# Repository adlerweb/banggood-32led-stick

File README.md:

This repository contains hardware documentation and software for Banggoods ["DIY 32 Bit LED Shake Stick Kit"](http://goo.gl/JAC3Vc). This repository is a supplement for [BitBastelei #205](https://www.adlerweb.info/blog/2016/07/24/bitbastelei-205-diy-32-bit-led-shake-stick-kit-banggood)(German).

# Hardware

The design itself is based on a [STC11F02E microcontroller](http://www.stcmcu.com/datasheet/stc/STC-AD-PDF/STC11F-10Fxx-english.pdf) (8051-compatible, 2KB Flash, 2KB EEPROM). All LEDs are connectred in a 3-way-matrix (lines, rows and polarity). An additional direction-switch and a push button are also available. The chip can be programmed using a serial connection which is available on a separate pin header.

Design notes:
 * While the battery case is build for 4xAA you should only use 3 and short the last one to avoid overvoltage. [See Instructions](http://forum.banggood.com/forum-topic-149391.html).
 * LEDs are not current limited and must be pulsed quickly to avoid damage
 * The IC is inteded for <=20mA and most likely overused

The provided design files can be opened using [KiCad](http://kicad-pcb.org/). The schematic schould be correct, the board layout is only a coarse drawing and should not be used as a reference without further checks 

# Software

The software is written in C and intended to be compiled using [sdcc](http://sdcc.sourceforge.net/). A project file for [MCU 8051 IDE](http://www.moravia-microsystems.com/mcu-8051-ide/) is included. Both tools are available for linux under a open source license, Windows-Versions should also be available.

In it's current state some basic functionallity is given, but the software is far from complere, see below for a list of known flaws.

## How the software works

At the top of the file a array of longs is defined. Every element represents one column of 32 LEDs, the left/highest bit will be drawn at the base of the unit. The first element will be drawn first. You can make the array wider or smaller using GRAPHSIZE above.

To draw a column the code will iterate every LED, switching the corresponding ports for LEDs to be lit either LOW or HIGH accordingly. LEDs and pins not used well be set to High-Z to avoid involuntary driving of other LEDs on the lines/columns of the LED-array. 

The main program will first inizialize all ports as inputs (High-Z) with an exception for both buttons which will be driven using the "quasi bidirectional" mode, allowing us to use the MCU as pull-up.

The main loop will start drawing once the push-button is pressed. This should be replaced with the direction switch for proper drawing. It will begin using the first array element and draw it several times. If the timeout is up it will continue with the second column, etc. Drawing will automatically stop when reaching the last element or releasing the button.

The timeout is calculated dynamically, the code will start with one and increase the number of repetition if the draw was finished before releasing the button (of later changing the direction again). Thes isn't really feasible when using the push-button but should somewhat work one the direction switch is used.

## How the software should work

Have a nice whish-list of things, that should be improved…

* Fix the direction-switch. I wasn't able to get the direction switch working right away and the push-button was enough for demonstration. Shouldn't be too much work
* The graph should be stored in EEPROM instead of flash memory as it is now - this should noticably increase available space and should allow for multiple graphs
* A more or less intelligent way to compress the graphs may also free up space, but I'm not sure if loosing the human-redability and a lot of processing power is worth the effort
* The 2-line-speed-algorithm may need a bit of care to be reliable
* Currently every LED is driven separatly. While this is easy to implement and keeps the current down it is also fscking slow. Grouping lines, columns or whatever should save execution time and allow for higher horizontal resolution and nicer text
*  It should be possible to implement a basic font and add a "programming mode" (power up with button pressed?) to allow for easier customization without the need to recompile the code every time

## Flashing

The IC can be programmed using a serial bootloader. You need a USB so TTL serial adapter to connect your PC to the board. Connect GND to GND, VCC to VCC/5V and cross RX/TX. On the software side you can use [stcgal](https://github.com/grigorig/stcgal) on linux or [the official tool](http://www.stcmcu.com/STCISP/stc-isp-15xx-v6.63.exe) for windows (which is afaik not in english…). You have to start the flashing process on your PC first and then powercycle the IC to enter the serial bootloader.

For Linux you can use this command:

```stcgal -P stc12 -p /dev/ttyUSB0 main.hex```

Yes, the LED-board is using a stc11-IC, but the protocol is identical. Please be aware you need full access to your serial programmer, depending on your setup you have to start the process as root or use sudo.

# Thanks

* [Banggood](http://banggood.com) for sponsoring the kit (and getting me to learn 8051-C)
* [Grigori Goronzy and all stcgal contributors](https://github.com/grigorig/stcgal) for saving me from wine with chinese fonts
* The team behind [sdcc](http://sdcc.sourceforge.net/) so I'm not required to write my own STC11 header files
* The guys behind [MCU 8051 IDE](http://www.moravia-microsystems.com/mcu-8051-ide/) so I hadn't to read the sdcc man page
* The whole [KiCad](http://kicad-pcb.org/) Folks because it still rocks
* You for providing patches, right? ;)

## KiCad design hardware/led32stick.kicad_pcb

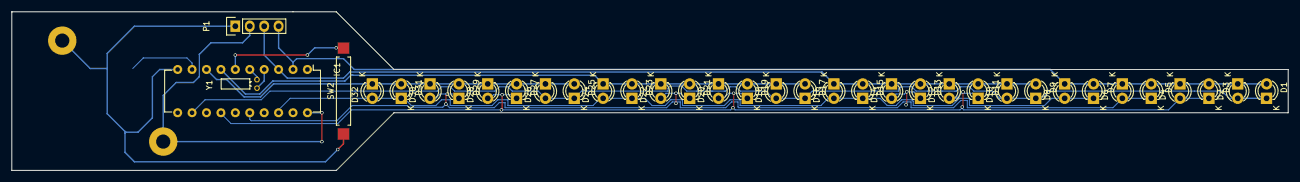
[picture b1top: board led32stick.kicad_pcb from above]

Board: 2 copper layers, 224.8 x 27.9 mm, 38 parts (1 on the bottom side), 14 nets.

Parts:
BT1: 3xAA; WireConnection_2.50mmDrill
D1, D2, D3, D4, D5, D6, D7, D8, D9, D10, D11, D12, D13, D14, D15, D16, D17, D18, D19, D20, D21, D22, D23, D24, D25, D26, D27, D28, D29, D30, D31, D32: LED; LED-3MM
IC1: STC11Fxx; DIP-20_W7.62mm
P1: CONN_01X04; Pin_Header_Straight_1x04
SW1: SW_PUSH; SW_SPST_B3S-1000
SW2: SPST; SW_SPST_REED_CT10-XXXX-G1
Y1: 12MHz; Crystal_Round_Horizontal_2mm

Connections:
GND: BT1.2, IC1.10, P1.1, SW1.2, SW2.2
unnamed: D1.1, D2.2, D9.1, D10.2, D17.1, D18.2, D25.1, D26.2, IC1.12
unnamed: D1.2, D2.1, D3.2, D4.1, D5.2, D6.1, D7.2, D8.1, IC1.2, P1.4
unnamed: D9.2, D10.1, D11.2, D12.1, D13.2, D14.1, D15.2, D16.1, IC1.3, P1.3
unnamed: D3.1, D4.2, D11.1, D12.2, D19.1, D20.2, D27.1, D28.2, IC1.14
unnamed: D5.1, D6.2, D13.1, D14.2, D21.1, D22.2, D29.1, D30.2, IC1.16
unnamed: D7.1, D8.2, D15.1, D16.2, D23.1, D24.2, D31.1, D32.2, IC1.18
unnamed: D17.2, D18.1, D19.2, D20.1, D21.2, D22.1, D23.2, D24.1, IC1.7
unnamed: D25.2, D26.1, D27.2, D28.1, D29.2, D30.1, D31.2, D32.1, IC1.8
unnamed: IC1.4, Y1.1
unnamed: IC1.5, Y1.2
unnamed: IC1.6, SW2.1
unnamed: IC1.9, SW1.1
VCC: BT1.1, IC1.20, P1.2

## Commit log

2016-07-23 Import Software
2016-07-23 Import Hardware
2016-07-23 License
2016-07-23 Readme
